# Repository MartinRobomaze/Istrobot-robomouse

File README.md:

## Welcome to GitHub Pages

You can use the [editor on GitHub](https://github.com/Martinlinux1/Istrobot-robomouse/edit/master/README.md) to maintain and preview the content for your website in Markdown files.

Whenever you commit to this repository, GitHub Pages will run [Jekyll](https://jekyllrb.com/) to rebuild the pages in your site, from the content in your Markdown files.

### Markdown

Markdown is a lightweight and easy-to-use syntax for styling your writing. It includes conventions for

```markdown
Syntax highlighted code block

# Header 1
## Header 2
### Header 3

- Bulleted
- List

1. Numbered
2. List

**Bold** and _Italic_ and `Code` text

[Link](url) and 
```

For more details see [GitHub Flavored Markdown](https://guides.github.com/features/mastering-markdown/).

### Jekyll Themes

Your Pages site will use the layout and styles from the Jekyll theme you have selected in your [repository settings](https://github.com/Martinlinux1/Istrobot-robomouse/settings). The name of this theme is saved in the Jekyll `_config.yml` configuration file.

### Support or Contact

Having trouble with Pages? Check out our [documentation](https://help.github.com/categories/github-pages-basics/) or [contact support](https://github.com/contact) and we’ll help you sort it out.

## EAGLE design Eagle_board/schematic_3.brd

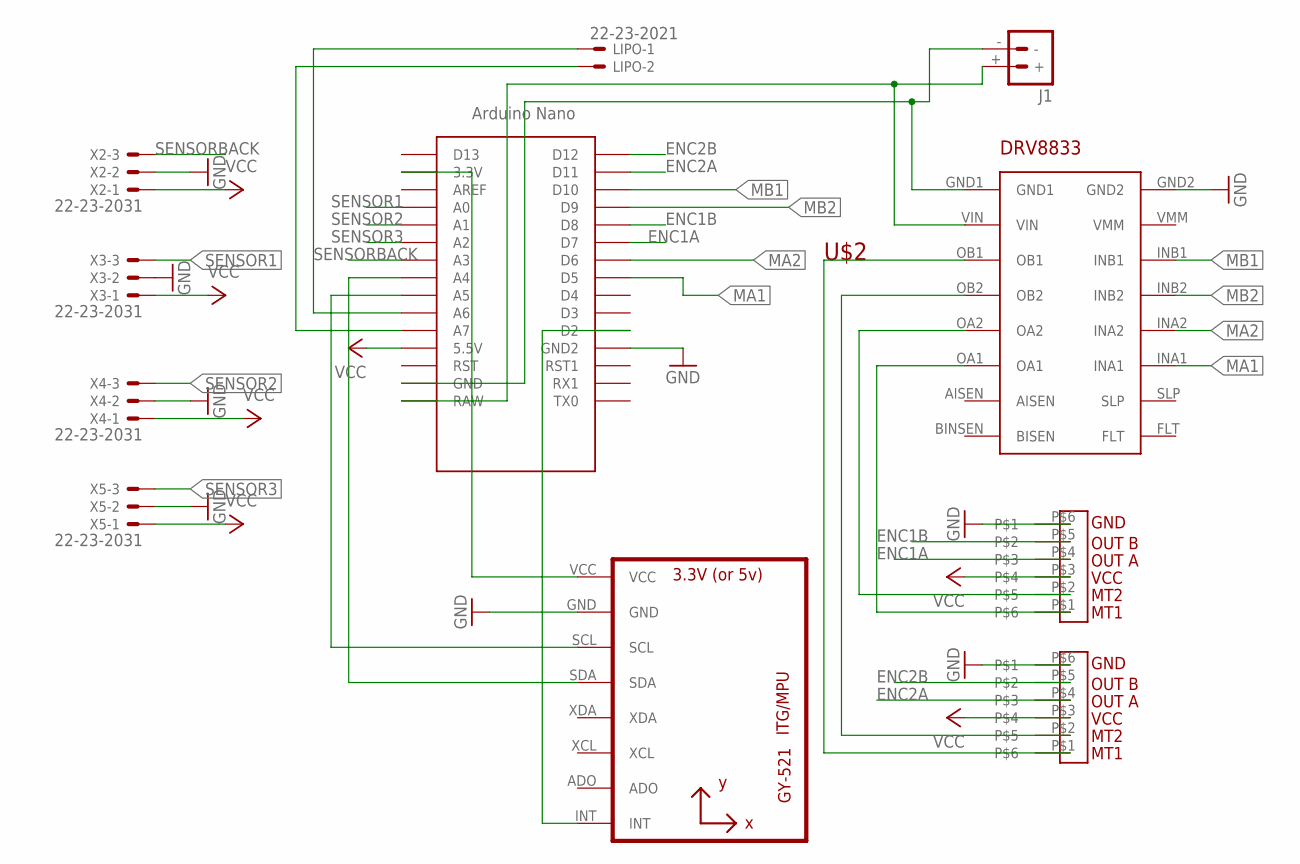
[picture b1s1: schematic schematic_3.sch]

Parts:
J1: BATTERY_CONN_DEANS; DEANS
LIPO: 22-23-2021
U1: GY-521MPU6050; GY-521
U$1: NANO
U$2: POLOLU-DRV8833
U$5, U$6: MOTOR; PINHEADER
X2, X3, X4, X5: 22-23-2031

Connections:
ENC1A: U$1.D7, U$5.P$4
ENC1B: U$1.D8, U$5.P$5
ENC2A: U$1.D11, U$6.P$4
ENC2B: U$1.D12, U$6.P$5
GND: U1.GND, U$1.GND1 (GND2), U$2.GND2, U$5.P$6, U$6.P$6, X2.2, X3.2, X4.2, X5.2
MA1: U$1.D5, U$2.INA1
MA2: U$1.D6, U$2.INA2
MB1: U$1.D10, U$2.INB1
MB2: U$1.D9, U$2.INB2
unnamed: J1.-, U$1.GND, U$2.GND1
unnamed: J1.+, U$1.RAW, U$2.VIN
unnamed: LIPO.1, U$1.A6
unnamed: LIPO.2, U$1.A7
unnamed: U1.VCC, U$1.3.3V
unnamed: U1.SCL, U$1.A5
unnamed: U1.SDA, U$1.A4
unnamed: U$2.OA2, U$5.P$2
unnamed: U$2.OA1, U$5.P$1
unnamed: U$2.OB2, U$6.P$2
unnamed: U$2.OB1, U$6.P$1
unnamed: U1.INT, U$1.D2
SENSOR1: U$1.A0, X3.3
SENSOR2: U$1.A1, X4.3
SENSOR3: U$1.A2, X5.3
SENSORBACK: U$1.A3, X2.3
VCC: U$1.5V (5.5V), U$5.P$3, U$6.P$3, X2.1, X3.1, X4.1, X5.1

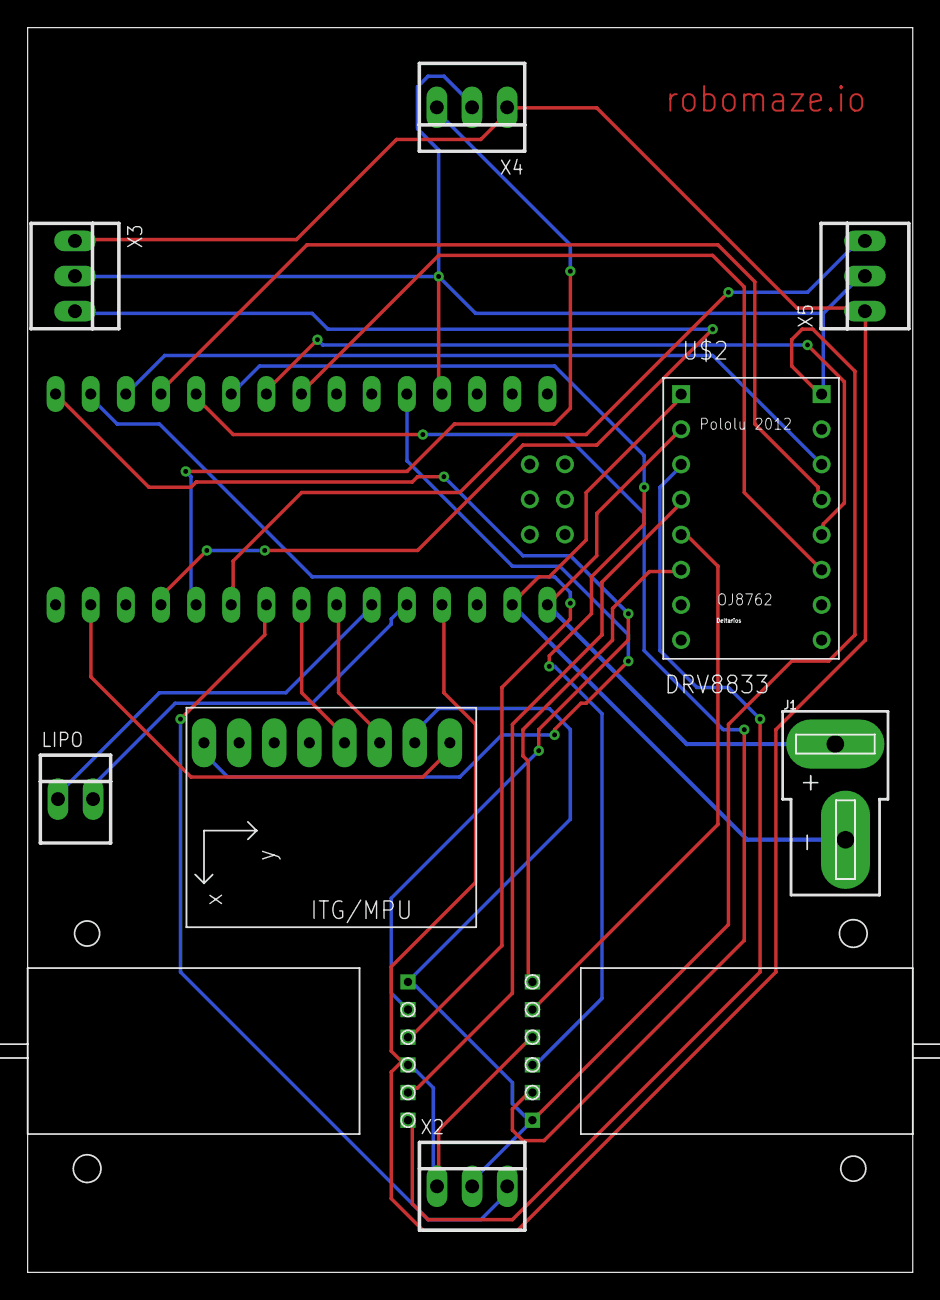
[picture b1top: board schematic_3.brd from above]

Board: 2 copper layers, 64.0 x 90.0 mm, 11 parts (0 on the bottom side), 26 nets.

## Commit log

2018-03-17 Made ArduinoInterface for communicate with arduino and tested motors
2018-03-31 ted encoders, finding issue with compass
2018-03-31 fixed issue with compass - replace it with gyro(mpu6050), testing gyro - sucesfull
2018-04-01 Added PCB and schematic
2018-04-01 finished PCB
2018-04-01 Set theme jekyll-theme-cayman
2018-04-01 Set theme jekyll-theme-slate
2018-04-11 --PIDcontrol

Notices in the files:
parts and their libraries:
SparkFun-Connectors: Licensing: Creative Commons ShareAlike 4.0 International - https://creativecommons.org/licenses/by-sa/4.0
